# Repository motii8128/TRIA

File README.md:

# TRIA
Triple-wheel Robot for Intelligent Autonomous

# install
```
sudo apt install nlohmann-json3-dev
sudo apt install protobuf-compiler
```

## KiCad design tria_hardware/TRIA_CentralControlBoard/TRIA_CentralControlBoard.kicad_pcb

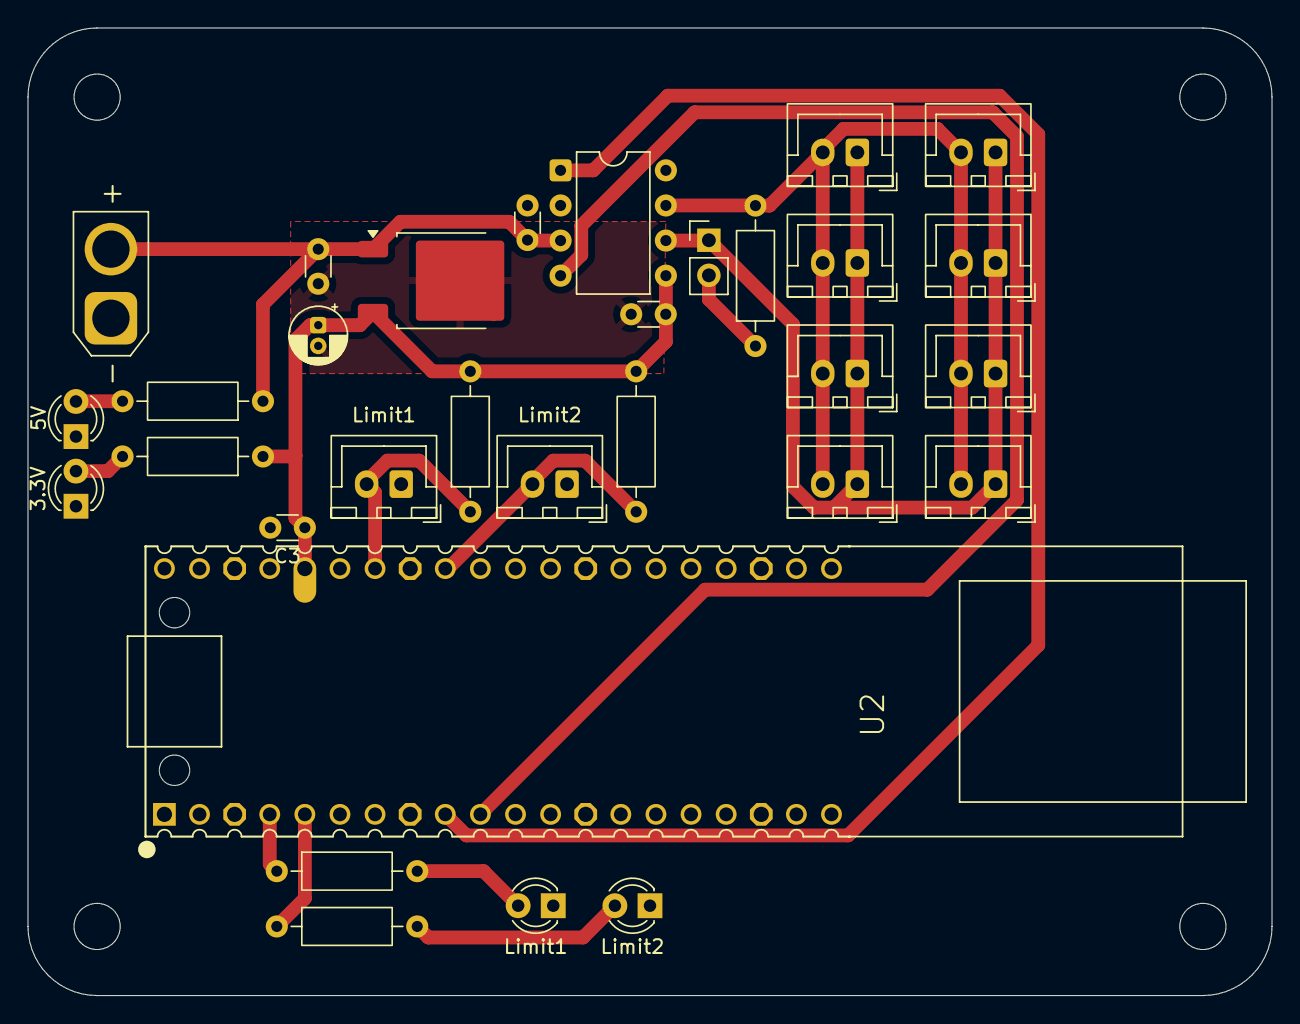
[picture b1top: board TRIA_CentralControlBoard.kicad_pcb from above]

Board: 2 copper layers, 90.0 x 70.0 mm, 31 parts (0 on the bottom side), 16 nets.

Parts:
3.3V: GREEN; LED_D3.0mm
5V: BLUE; LED_D3.0mm
C1, C3, C14, C15: 0.1u; C_Disc_D3.0mm_W1.6mm_P2.50mm
C2: 10uF16V; CP_Radial_D4.0mm_P1.50mm
J1, J3, J4, J6, J7, J8, J9, J10: CAN; JST_XH_B2B-XH-A_1x02_P2.50mm_Vertical
J2: LogicBatt; AMASS_XT30U-M_1x02_P5.0mm_Vertical
J5: resistor_enable; PinHeader_1x02_P2.54mm_Vertical
Limit1: limit_switch1; JST_XH_B2B-XH-A_1x02_P2.50mm_Vertical
Limit1#2, Limit2#2: RED; LED_D3.0mm
Limit2: limit_switch2; JST_XH_B2B-XH-A_1x02_P2.50mm_Vertical
R1, R2: 10k; R_Axial_DIN0207_L6.3mm_D2.5mm_P10.16mm_Horizontal
R3, R4, R5, R6: 1k; R_Axial_DIN0207_L6.3mm_D2.5mm_P10.16mm_Horizontal
R17: 120; R_Axial_DIN0207_L6.3mm_D2.5mm_P10.16mm_Horizontal
U1: NJM2391DL1-33; TO-252-2
U2: W6300-EVB-PICO2; W5500-EVB-PICO-TH
U9: MCP2562-E-P; DIP-8_W7.62mm

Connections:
+3.3V: C2.1, C3.1, C14.1, R1.2, R2.2, R4.1, U1.3 (VO), U2.36 (3V3(OUT)), U9.5 (Vio)
/CAN/CAN_H: J1.2, J3.2, J4.2, J6.2, J7.2, J8.2, J9.2, J10.2, R17.2, U9.7 (CANH)
/CAN/CAN_L: J1.1, J3.1, J4.1, J5.1, J6.1, J7.1, J8.1, J9.1, J10.1, U9.6 (CANL)
/CAN/CAN_RX: U2.10 (GP7), U9.4 (RXD)
/CAN/CAN_TX: U2.9 (GP6), U9.1 (TXD)
/Limit_Switch/LimitSwitch1: Limit1.2, R1.1, U2.34 (GP28)
/Limit_Switch/LimitSwitch2: Limit2.2, R2.1, U2.32 (GP27)
GNDD: 3.3V.1 (K), 5V.1 (K), C1.2, C2.2, C3.2, C14.2, C15.2, J2.1, Limit1.1, Limit1#2.1 (K), Limit2.1, Limit2#2.1 (K), U1.2 (GND), U2.3 (GND), U2.8 (GND), U2.13 (GND), U2.18 (GND), U2.23 (GND), U2.28 (GND), U2.33 (GND), U2.37 (3V3_EN), U2.38 (GND), U9.2 (VSS), U9.8 (STBY)
LED1: R5.1, U2.4 (GP2)
LED2: R6.1, U2.5 (GP3)
unnamed: 5V.2 (A), R3.2
unnamed: 3.3V.2 (A), R4.2
unnamed: Limit1#2.2 (A), R5.2
unnamed: Limit2#2.2 (A), R6.2
unnamed: J5.2, R17.1
VDD: C1.1, C15.1, J2.2, R3.1, U1.1 (VI), U9.3 (VDD)

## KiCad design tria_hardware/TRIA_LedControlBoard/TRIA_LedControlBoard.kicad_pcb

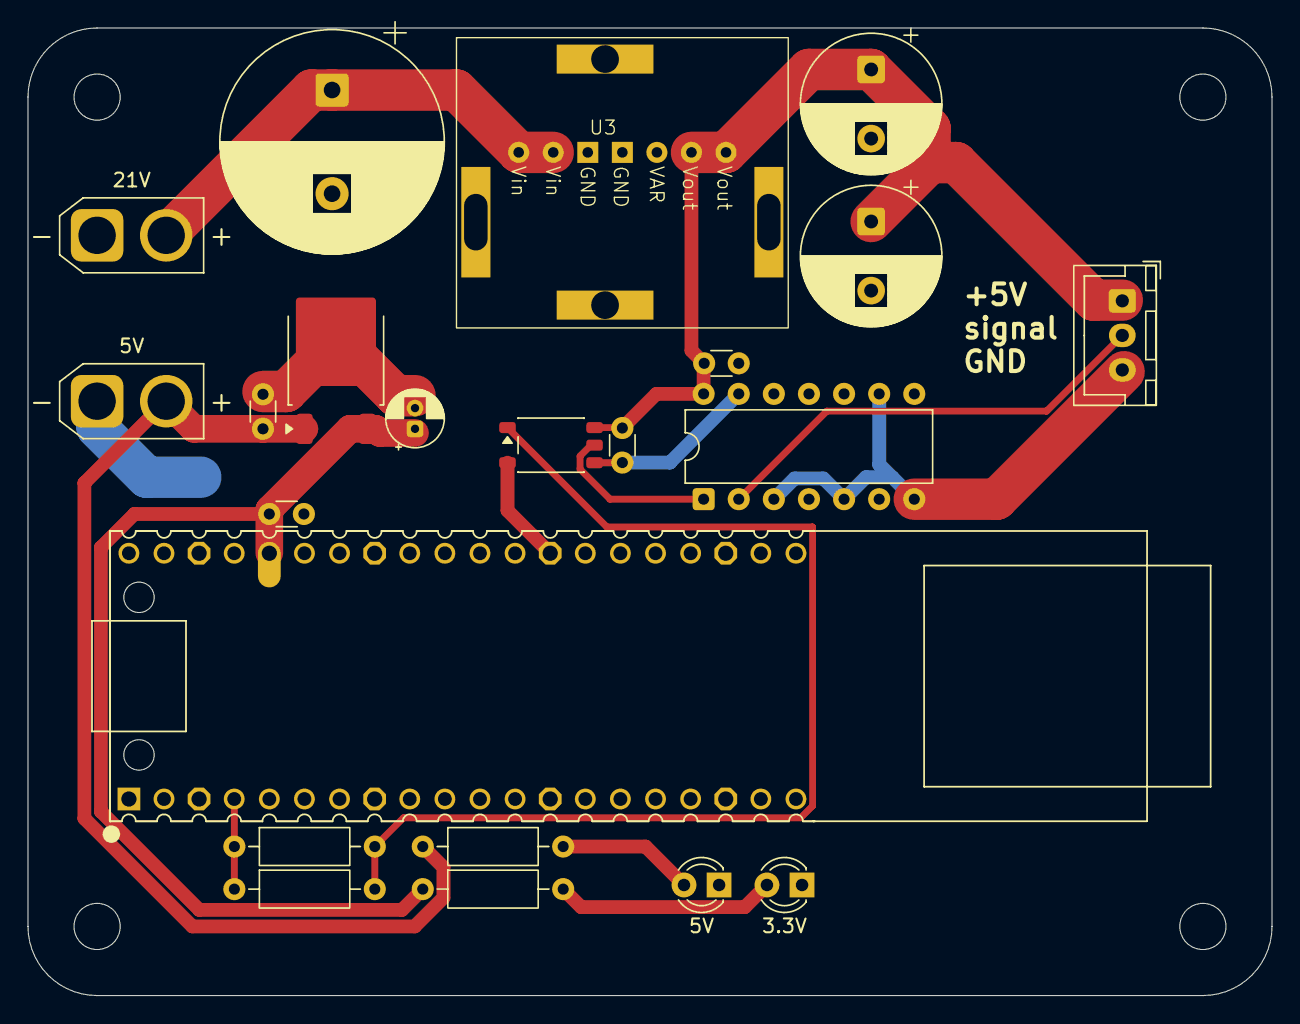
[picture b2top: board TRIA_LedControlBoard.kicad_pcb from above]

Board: 2 copper layers, 90.0 x 70.0 mm, 22 parts (0 on the bottom side), 12 nets.

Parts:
3.3V: GREEN; LED_D3.0mm
5V: LogicBatt; AMASS_XT30U-M_1x02_P5.0mm_Vertical
5V#2: BLUE; LED_D3.0mm
21V: DriveBatt; AMASS_XT30U-M_1x02_P5.0mm_Vertical
C1, C3, C7, C8: 0.1u; C_Disc_D3.0mm_W1.6mm_P2.50mm
C2: 10uF16V; CP_Radial_D4.0mm_P1.50mm
C4: 1000uF50V; CP_Radial_D16.0mm_P7.50mm
C5, C6: 1000uF25V; CP_Radial_D10.0mm_P5.00mm
R1, R2, R3, R4: 1k; R_Axial_DIN0207_L6.3mm_D2.5mm_P10.16mm_Horizontal
U1: NJM2391DL1-33; TO-252-2
U2: W6300-EVB-PICO2; W5500-EVB-PICO-TH
U3: MPD7K020S
U4: TLP2361; SO-5-6_4.55x3.7mm_P1.27mm
U5: 74HC04; DIP-14_W7.62mm
WS2812: WS2812; JST_XH_B3B-XH-A_1x03_P2.50mm_Vertical

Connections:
+3.3V: C2.1, C3.1, R4.1, U1.3 (VO), U2.36 (3V3(OUT))
+5V: C5.1, C6.1, C7.1, C8.1, U3.6 (Vout), U3.7 (Vout), U4.6 (VDD), U5.14 (VCC), WS2812.1
+BATT: 21V.2, C4.1, U3.1 (Vin), U3.2 (Vin)
/PhotoCoupler/signal_in: R1.1, R2.1, U2.4 (GP2)
/PhotoCoupler/signal_out: U5.2, WS2812.2
GND: 21V.1, C4.2, C5.2, C6.2, C7.2, C8.2, U3.3 (GND), U3.4 (GND), U4.4 (GND), U5.3, U5.5, U5.7 (GND), U5.9, U5.11, U5.13, WS2812.3
GNDD: 3.3V.1 (K), 5V.1, 5V#2.1 (K), C1.2, C2.2, C3.2, U1.2 (GND), U2.3 (GND), U2.8 (GND), U2.13 (GND), U2.18 (GND), U2.23 (GND), U2.28 (GND), U2.33 (GND), U2.37 (3V3_EN), U2.38 (GND), U4.3 (K)
unnamed: 5V#2.2 (A), R3.2
unnamed: 3.3V.2 (A), R4.2
unnamed: R1.2, R2.2, U4.1 (A)
unnamed: U4.5 (VO), U5.1
VDD: 5V.2, C1.1, R3.1, U1.1 (VI)

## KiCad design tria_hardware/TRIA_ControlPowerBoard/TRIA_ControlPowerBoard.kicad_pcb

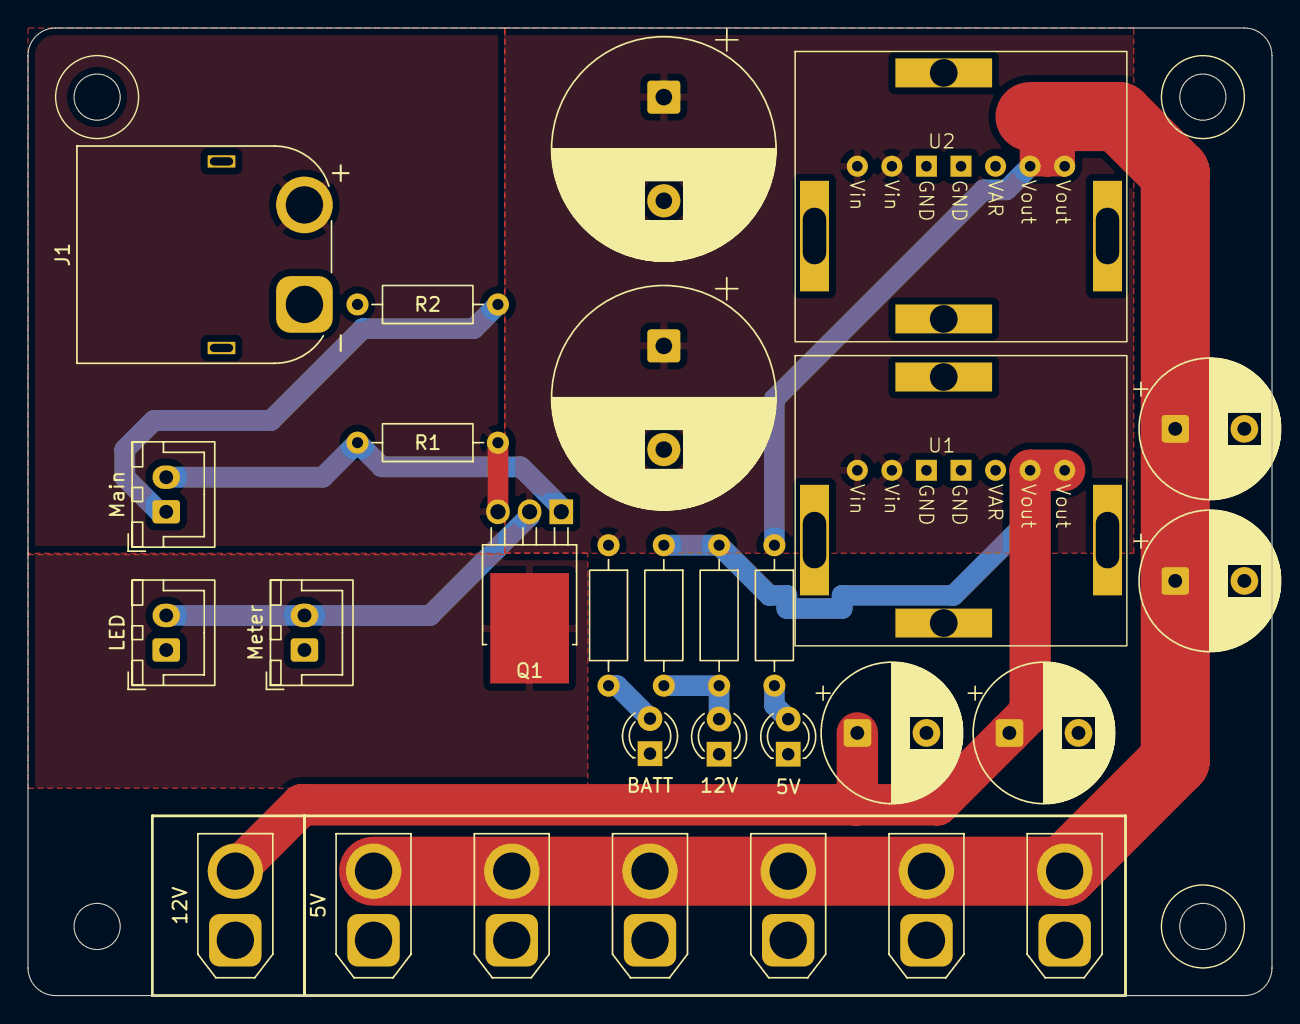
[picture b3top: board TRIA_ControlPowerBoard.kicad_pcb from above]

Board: 2 copper layers, 90.0 x 70.0 mm, 29 parts (0 on the bottom side), 10 nets.

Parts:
5V: GREEN; LED_D3.0mm
5V#2: out5V; AMASS_XT30U-F_1x02_P5.0mm_Vertical
12V: out12V; AMASS_XT30U-F_1x02_P5.0mm_Vertical
12V#2: RED; LED_D3.0mm
BATT: BLUE; LED_D3.0mm
C1, C4: 1000uF50V; CP_Radial_D16.0mm_P7.50mm
C2, C3, C5, C6: 1000uF25V; CP_Radial_D10.0mm_P5.00mm
J1: Batt; AMASS_XT60PW-M_1x02_P7.20mm_Horizontal
J2, J4, J8, J9, J10: out5V; AMASS_XT30U-F_1x02_P5.0mm_Vertical
LED: SW_LED; JST_XH_B2B-XH-A_1x02_P2.50mm_Vertical
Main: power_swtich; JST_XH_B2B-XH-A_1x02_P2.50mm_Vertical
Meter: voltage_meter; JST_XH_B2B-XH-A_1x02_P2.50mm_Vertical
Q1: MTP4835I3; TO-251-3-1EP_Horizontal_TabDown
R1, R2: 10k; R_Axial_DIN0207_L6.3mm_D2.5mm_P10.16mm_Horizontal
R3, R4, R5: 1k; R_Axial_DIN0207_L6.3mm_D2.5mm_P10.16mm_Horizontal
R6: 120; R_Axial_DIN0207_L6.3mm_D2.5mm_P10.16mm_Horizontal
U1, U2: MPD7K020S

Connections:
+5V: 5V#2.2, C5.1, C6.1, J2.2, J4.2, J8.2, J9.2, J10.2, R6.1, U2.6 (Vout), U2.7 (Vout)
+12V: 12V.2, C2.1, C3.1, R4.1, R5.1, U1.6 (Vout), U1.7 (Vout)
+BATT: C1.1, C4.1, LED.2, Meter.2, Q1.1 (D), R3.1, U1.1 (Vin), U1.2 (Vin), U2.1 (Vin), U2.2 (Vin)
GND: 5V.1 (K), 5V#2.1, 12V.1, 12V#2.1 (K), BATT.1 (K), C1.2, C2.2, C3.2, C4.2, C5.2, C6.2, J1.1, J2.1, J4.1, J8.1, J9.1, J10.1, LED.1, Meter.1, R2.2, U1.3 (GND), U1.4 (GND), U1.5 (VAR), U2.3 (GND), U2.4 (GND)
unnamed: BATT.2 (A), R3.2
unnamed: 12V#2.2 (A), R4.2, R5.2
unnamed: 5V.2 (A), R6.2
unnamed: J1.2, Q1.3 (S), R1.1
unnamed: Main.1, R2.1
unnamed: Main.2, Q1.2 (G), R1.2

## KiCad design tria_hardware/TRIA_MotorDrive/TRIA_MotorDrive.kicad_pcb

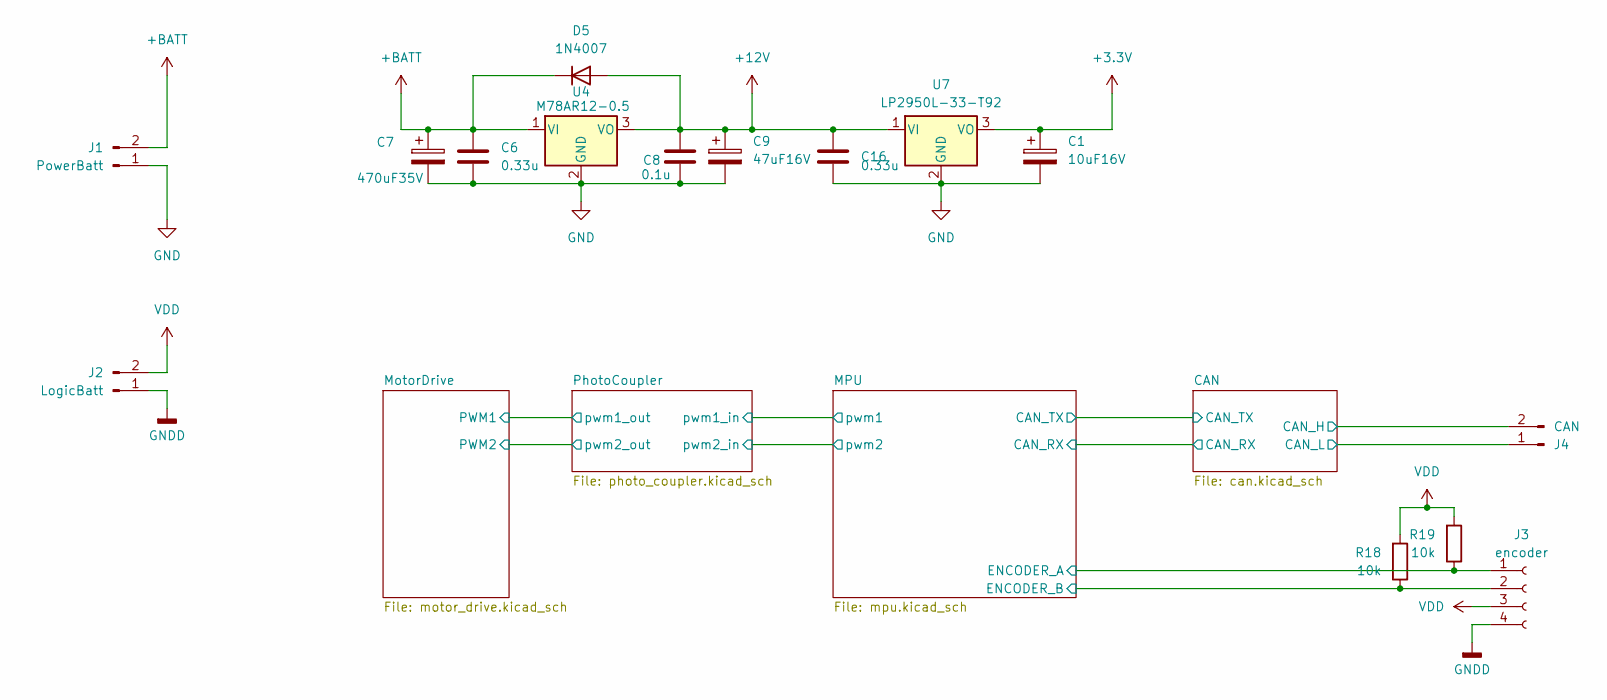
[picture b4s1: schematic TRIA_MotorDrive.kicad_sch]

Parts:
C1: 10uF16V; CP_Radial_D4.0mm_P1.50mm
C6, C16: 0.33u; C_Disc_D3.0mm_W1.6mm_P2.50mm
C7: 470uF35V; CP_Radial_D10.0mm_P5.00mm
C8: 0.1u; C_Disc_D3.0mm_W1.6mm_P2.50mm
C9: 47uF16V; CP_Radial_D5.0mm_P2.00mm
D5: 1N4007; D_DO-41_SOD81_P7.62mm_Horizontal
J1: PowerBatt; AMASS_XT60-M_1x02_P7.20mm_Vertical
J2: LogicBatt; AMASS_XT30U-M_1x02_P5.0mm_Vertical
J3: encoder; JST_XH_B4B-XH-A_1x04_P2.50mm_Vertical
J4: CAN; JST_XH_B2B-XH-A_1x02_P2.50mm_Vertical
R18, R19: 10k; R_Axial_DIN0207_L6.3mm_D2.5mm_P10.16mm_Horizontal
U4: M78AR12-0.5; m78ar033-1
U7: LP2950L-33-T92; TO-92L_Inline

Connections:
+3.3V: C1.1, U7.3 (VO); also elsewhere on the board
+12V: C8.1, C9.1, C16.1, D5.2 (A), U4.3 (VO), U7.1 (VI)
+BATT: C6.1, C7.1, D5.1 (K), J1.2, U4.1 (VI); also elsewhere on the board
/CAN/CAN_H: J4.2; also elsewhere on the board
/CAN/CAN_L: J4.1; also elsewhere on the board
/MPU/ENCODER_A: J3.1, R19.1; also elsewhere on the board
/MPU/ENCODER_B: J3.2, R18.1; also elsewhere on the board
GND: C1.2, C6.2, C7.2, C8.2, C9.2, C16.2, J1.1, U4.2 (GND), U7.2 (GND); also elsewhere on the board
GNDD: J2.1, J3.4; also elsewhere on the board
VDD: J2.2, J3.3, R18.2, R19.2; also elsewhere on the board

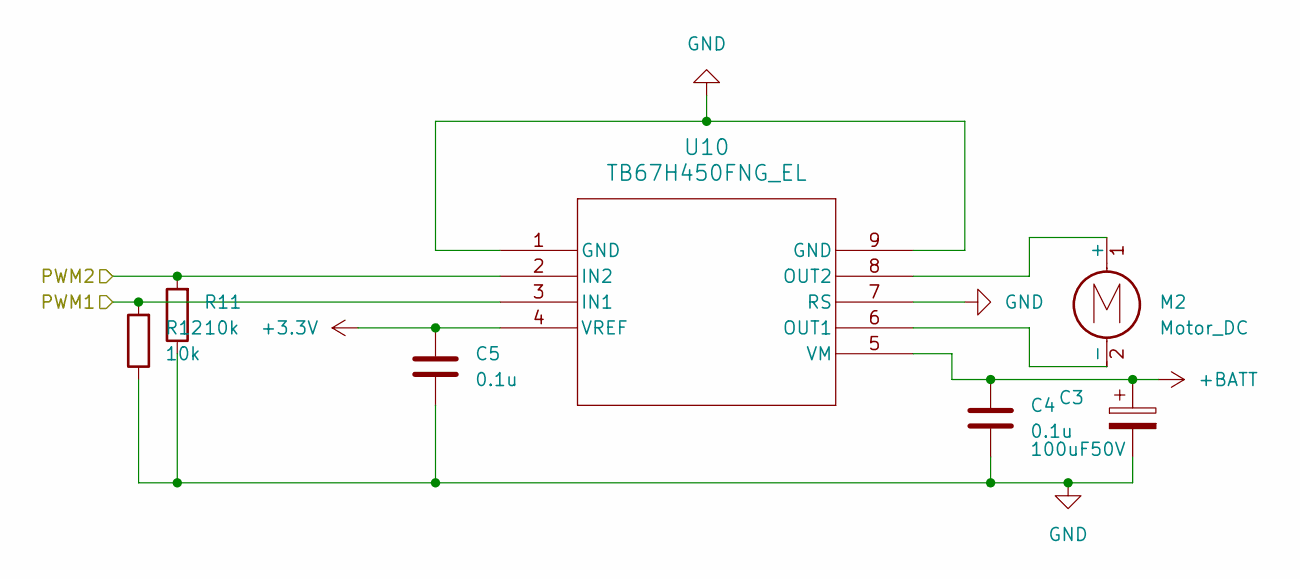
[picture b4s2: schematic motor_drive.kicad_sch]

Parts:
C3: 100uF50V; CP_Radial_D8.0mm_P3.50mm
C4, C5: 0.1u; C_Disc_D3.0mm_W1.6mm_P2.50mm
M2: Motor_DC; AMASS_XT60-F_1x02_P7.20mm_Vertical
R11, R12: 10k; R_Axial_DIN0207_L6.3mm_D2.5mm_P10.16mm_Horizontal
U10: TB67H450FNG_EL; P-HSOP8-0405-1p27-002_TOS

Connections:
+3.3V: C5.1, U10.4 (VREF); also elsewhere on the board
+BATT: C3.1, C4.1, U10.5 (VM); also elsewhere on the board
/MotorDrive/PWM1: R12.2, U10.3 (IN1); also elsewhere on the board
/MotorDrive/PWM2: R11.2, U10.2 (IN2); also elsewhere on the board
GND: C3.2, C4.2, C5.2, R11.1, R12.1, U10.1 (GND), U10.7 (RS), U10.9 (GND); also elsewhere on the board
unnamed: M2.1 (+), U10.8 (OUT2)
unnamed: M2.2 (-), U10.6 (OUT1)

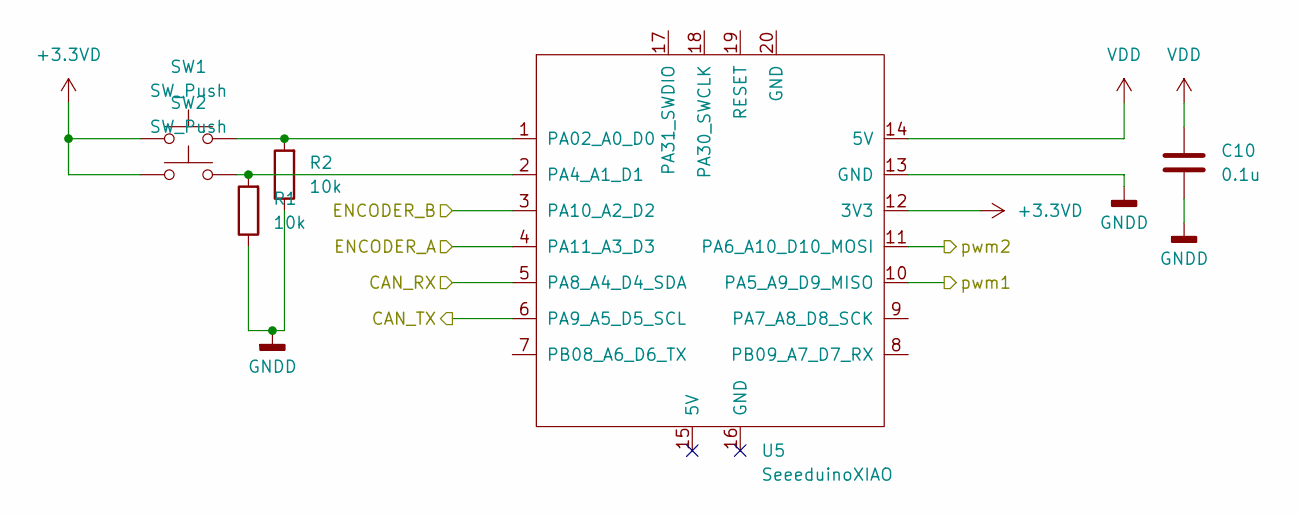
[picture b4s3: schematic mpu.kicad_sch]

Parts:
C10: 0.1u; C_Disc_D3.0mm_W1.6mm_P2.50mm
R1, R2: 10k; R_Axial_DIN0207_L6.3mm_D2.5mm_P10.16mm_Horizontal
SW1, SW2: SW_Push; SW_PUSH_6mm
U5: SeeeduinoXIAO; Seeeduino XIAO-MOUDLE14P-2.54-21X17.8MM

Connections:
+3.3VD: SW1.1, SW2.1, U5.12 (3V3); also elsewhere on the board
/CAN/CAN_RX: U5.5 (PA8_A4_D4_SDA); also elsewhere on the board
/CAN/CAN_TX: U5.6 (PA9_A5_D5_SCL); also elsewhere on the board
/MPU/ENCODER_A: U5.4 (PA11_A3_D3); also elsewhere on the board
/MPU/ENCODER_B: U5.3 (PA10_A2_D2); also elsewhere on the board
/MPU/pwm1: U5.10 (PA5_A9_D9_MISO); also elsewhere on the board
/MPU/pwm2: U5.11 (PA6_A10_D10_MOSI); also elsewhere on the board
GNDD: C10.2, R1.1, R2.1, U5.13 (GND); also elsewhere on the board
unnamed: R2.2, SW1.2, U5.1 (PA02_A0_D0)
unnamed: R1.2, SW2.2, U5.2 (PA4_A1_D1)
VDD: C10.1, U5.14 (5V); also elsewhere on the board

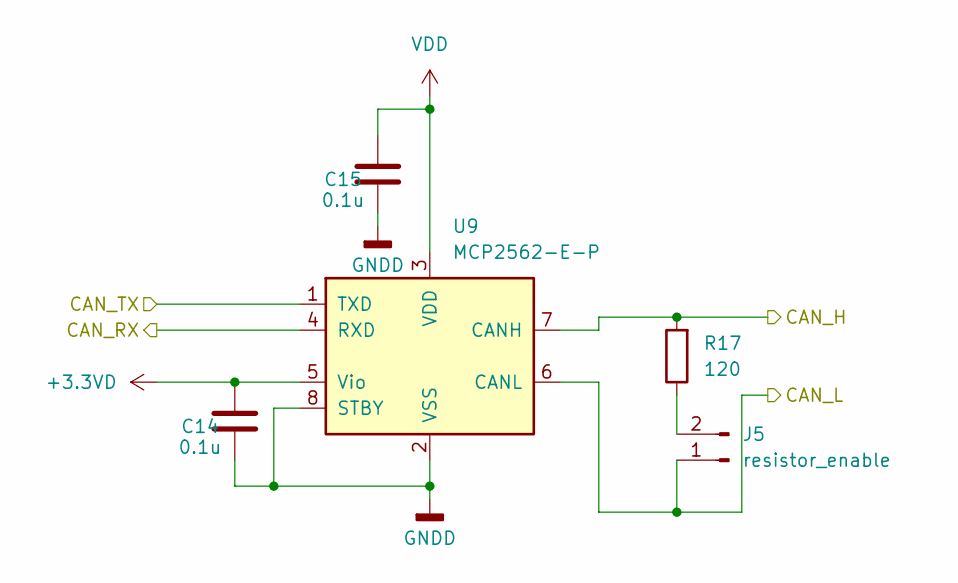
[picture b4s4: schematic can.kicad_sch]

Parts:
C14, C15: 0.1u; C_Disc_D3.0mm_W1.6mm_P2.50mm
J5: resistor_enable; PinHeader_1x02_P2.54mm_Vertical
R17: 120; R_Axial_DIN0207_L6.3mm_D2.5mm_P10.16mm_Horizontal
U9: MCP2562-E-P; DIP-8_W7.62mm

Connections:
+3.3VD: C14.1, U9.5 (Vio); also elsewhere on the board
/CAN/CAN_H: R17.2, U9.7 (CANH); also elsewhere on the board
/CAN/CAN_L: J5.1, U9.6 (CANL); also elsewhere on the board
/CAN/CAN_RX: U9.4 (RXD); also elsewhere on the board
/CAN/CAN_TX: U9.1 (TXD); also elsewhere on the board
GNDD: C14.2, C15.2, U9.2 (VSS), U9.8 (STBY); also elsewhere on the board
unnamed: J5.2, R17.1
VDD: C15.1, U9.3 (VDD); also elsewhere on the board

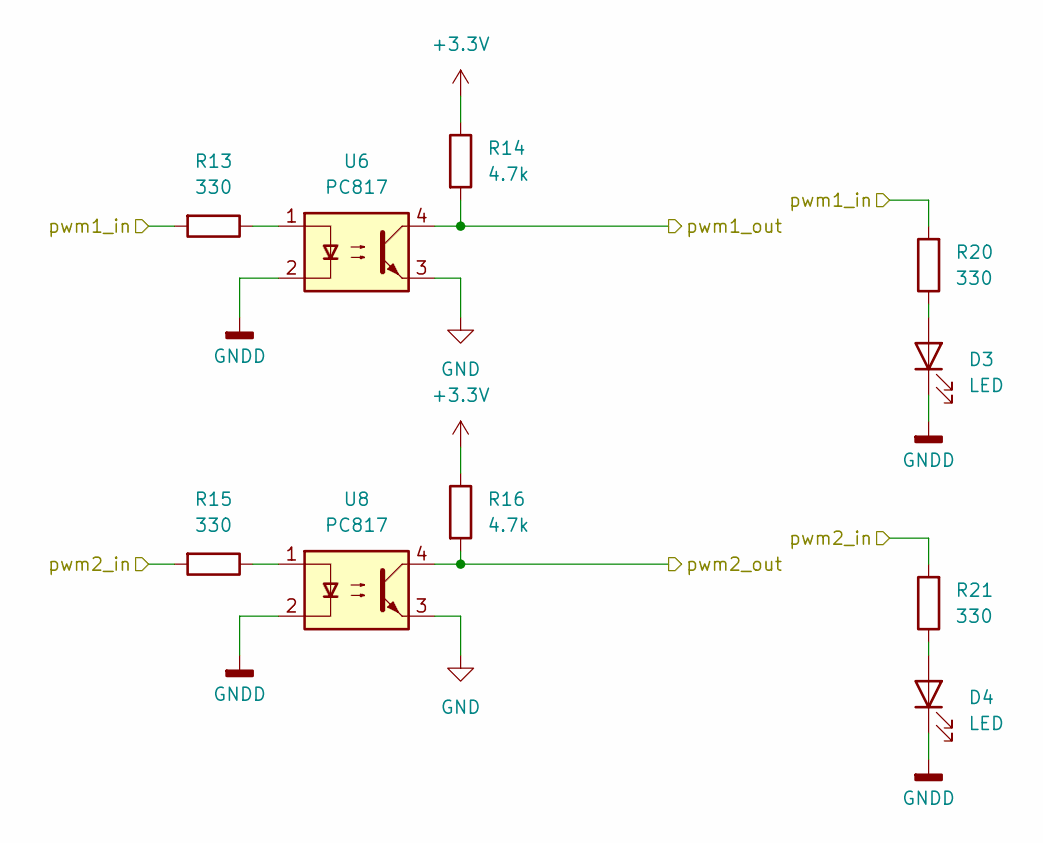
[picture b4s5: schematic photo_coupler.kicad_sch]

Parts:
D3, D4: LED; LED_D3.0mm
R13, R15, R20, R21: 330; R_1206_3216Metric_Pad1.30x1.75mm_HandSolder
R14, R16: 4.7k; R_1206_3216Metric_Pad1.30x1.75mm_HandSolder
U6, U8: PC817; DIP-4_W7.62mm

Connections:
+3.3V: R14.1, R16.1; also elsewhere on the board
/MPU/pwm1: R13.2, R20.2; also elsewhere on the board
/MPU/pwm2: R15.2, R21.2; also elsewhere on the board
/MotorDrive/PWM1: R14.2, U6.4; also elsewhere on the board
/MotorDrive/PWM2: R16.2, U8.4; also elsewhere on the board
GND: U6.3, U8.3; also elsewhere on the board
GNDD: D3.1 (K), D4.1 (K), U6.2, U8.2; also elsewhere on the board
unnamed 16: D3.2 (A), R20.1; also elsewhere on the board
unnamed 17: D4.2 (A), R21.1; also elsewhere on the board
unnamed: R13.1, U6.1
unnamed: R15.1, U8.1

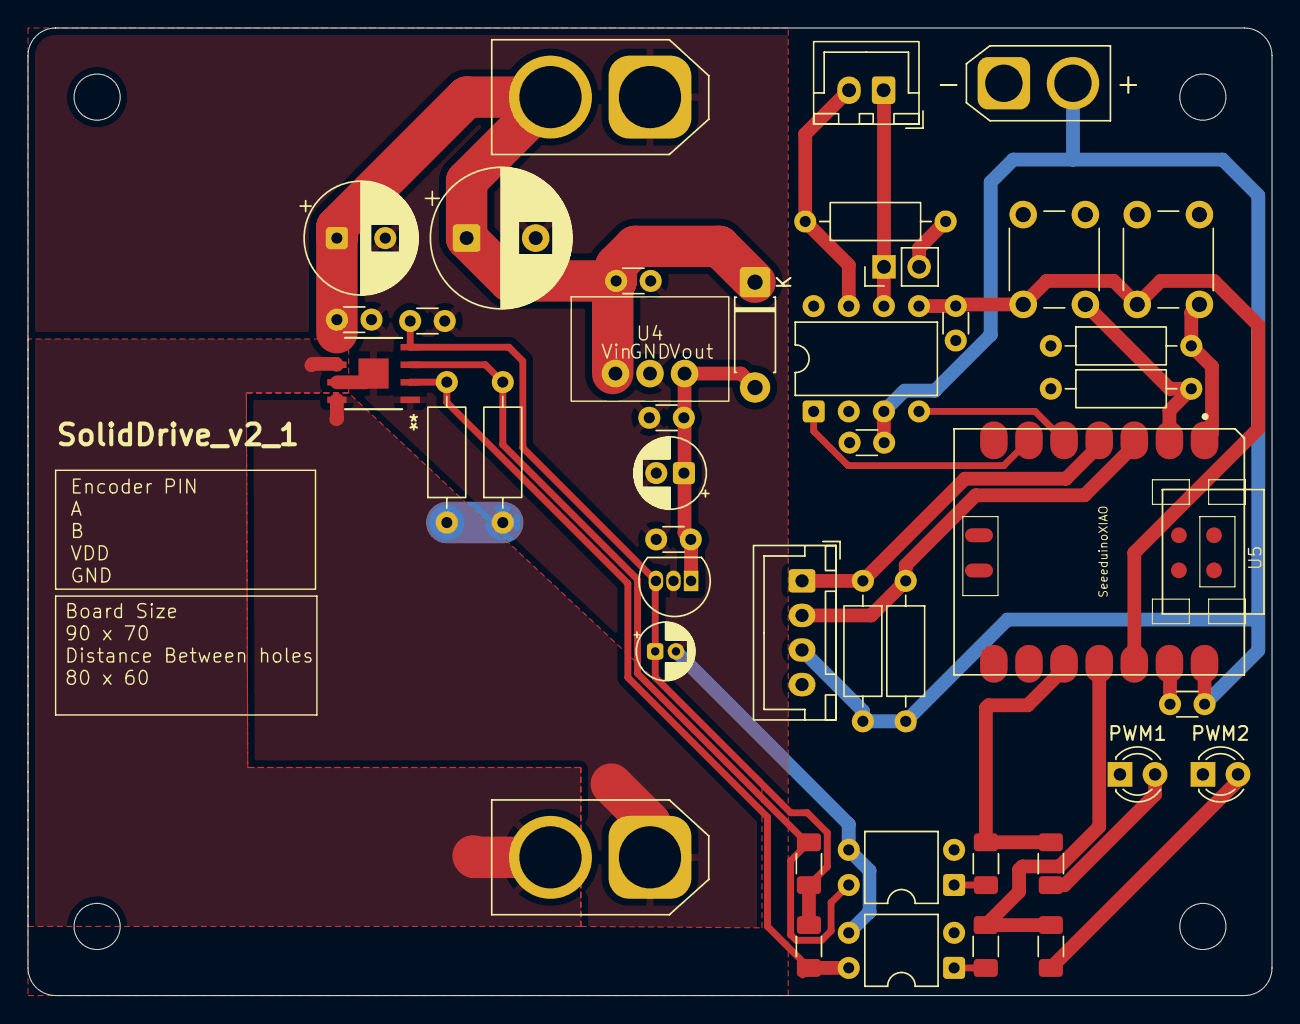
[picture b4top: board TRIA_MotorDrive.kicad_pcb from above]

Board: 2 copper layers, 90.0 x 70.0 mm, 43 parts (0 on the bottom side), 26 nets.

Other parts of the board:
PWM1, PWM2: LED; LED_D3.0mm

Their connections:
GNDD: PWM1.1 (K), PWM2.1 (K); also elsewhere on the board
unnamed 16: PWM1.2 (A); also elsewhere on the board
unnamed 17: PWM2.2 (A); also elsewhere on the board

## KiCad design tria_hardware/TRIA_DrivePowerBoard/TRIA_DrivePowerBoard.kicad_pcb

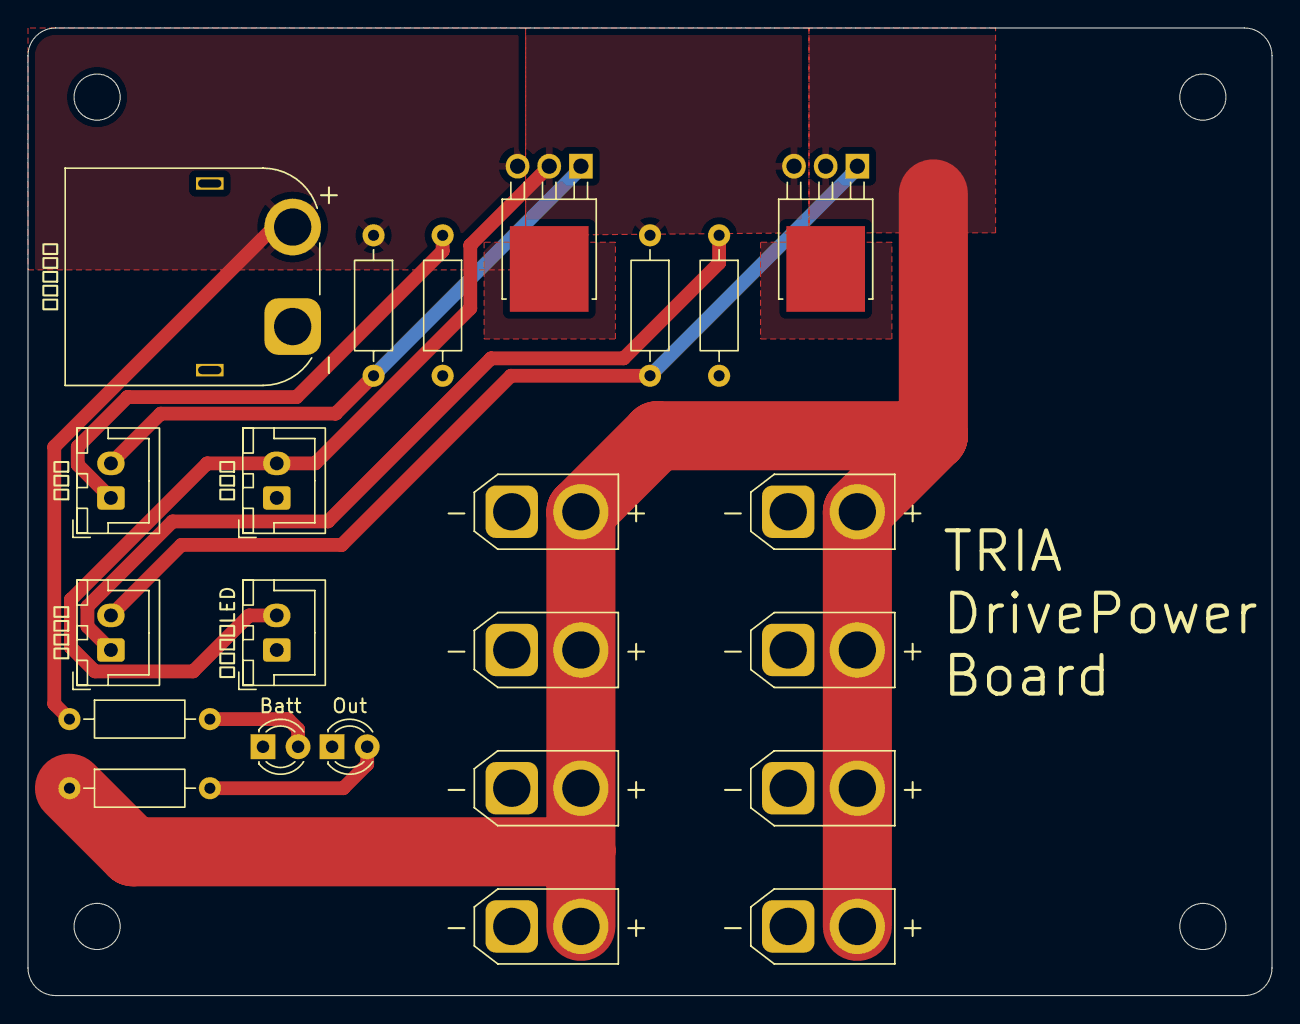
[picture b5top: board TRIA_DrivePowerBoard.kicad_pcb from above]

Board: 2 copper layers, 90.0 x 70.0 mm, 23 parts (0 on the bottom side), 10 nets.

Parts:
Batt: BLUE; LED_D3.0mm
J3, J4, J5, J8, J9, J10, J11, J12: out; AMASS_XT30U-F_1x02_P5.0mm_Vertical
Out: Green; LED_D3.0mm
Q1, Q2: MTP4835I3; TO-251-3-1EP_Horizontal_TabDown
R1, R2, R3, R4: 10k; R_Axial_DIN0207_L6.3mm_D2.5mm_P10.16mm_Horizontal
R5, R6: 1k; R_Axial_DIN0207_L6.3mm_D2.5mm_P10.16mm_Horizontal
スイッチLED: sw_led; JST_XH_B2B-XH-A_1x02_P2.50mm_Vertical
バッテリー: Batt; AMASS_XT60PW-M_1x02_P7.20mm_Horizontal
主電源: power_swtich; JST_XH_B2B-XH-A_1x02_P2.50mm_Vertical
緊急停止: emergency; JST_XH_B2B-XH-A_1x02_P2.50mm_Vertical
電圧計: voltage_meter; JST_XH_B2B-XH-A_1x02_P2.50mm_Vertical

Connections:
+BATT: Q1.3 (S), R1.1, R5.1, バッテリー.2
GND: Batt.1 (K), J3.1, J4.1, J5.1, J8.1, J9.1, J10.1, J11.1, J12.1, Out.1 (K), R2.2, R4.2, スイッチLED.1, バッテリー.1, 電圧計.1
unnamed: Batt.2 (A), R5.2
unnamed: Out.2 (A), R6.2
unnamed: R4.1, 緊急停止.1
unnamed: Q2.2 (G), R3.2, 緊急停止.2
unnamed: R2.1, 主電源.1
unnamed: Q1.2 (G), R1.2, 主電源.2
non_emergency: Q1.1 (D), Q2.3 (S), R3.1, スイッチLED.2, 電圧計.2
out: J3.2, J4.2, J5.2, J8.2, J9.2, J10.2, J11.2, J12.2, Q2.1 (D), R6.1

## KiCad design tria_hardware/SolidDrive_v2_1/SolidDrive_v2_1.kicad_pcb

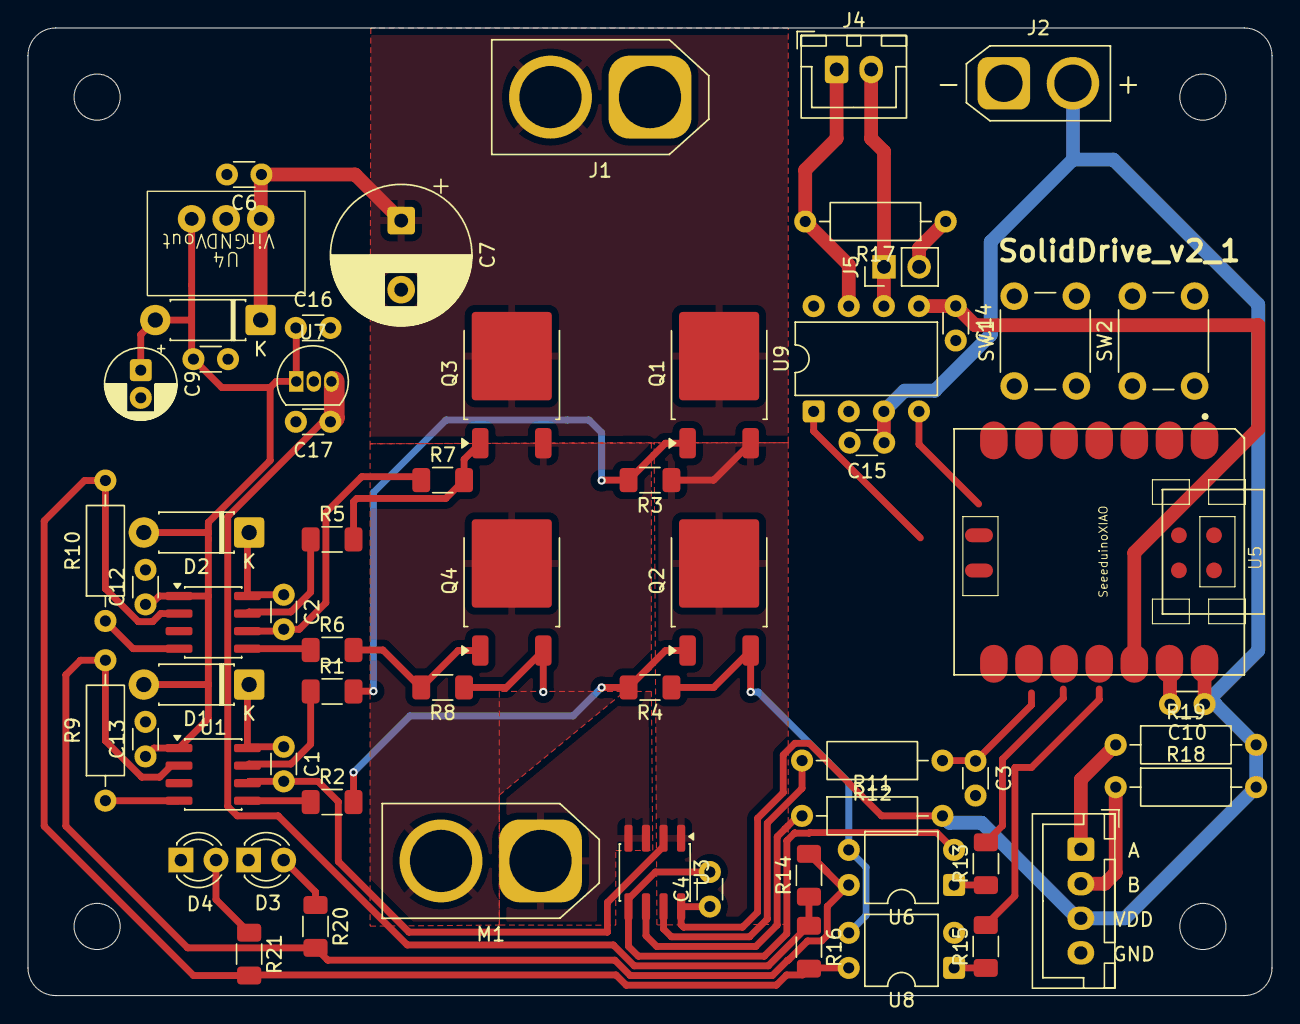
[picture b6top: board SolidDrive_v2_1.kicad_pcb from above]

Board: 2 copper layers, 90.0 x 70.0 mm, 62 parts (0 on the bottom side), 35 nets.

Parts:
C1, C2: 1u; C_Disc_D3.0mm_W1.6mm_P2.50mm
C3, C4, C8, C10, C12, C13, C14, C15, C17: 0.1u; C_Disc_D3.0mm_W1.6mm_P2.50mm
C6, C16: 0.33u; C_Disc_D3.0mm_W1.6mm_P2.50mm
C7: 470uF35V; CP_Radial_D10.0mm_P5.00mm
C9: 47uF16V; CP_Radial_D5.0mm_P2.00mm
D1, D2: 1N5819; D_DO-41_SOD81_P7.62mm_Horizontal
D3, D4: LED; LED_D3.0mm
D5: 1N4007; D_DO-41_SOD81_P7.62mm_Horizontal
J1: PowerBatt; AMASS_XT60-M_1x02_P7.20mm_Vertical
J2: LogicBatt; AMASS_XT30U-M_1x02_P5.0mm_Vertical
J3: encoder; JST_XH_B4B-XH-A_1x04_P2.50mm_Vertical
J4: CAN; JST_XH_B2B-XH-A_1x02_P2.50mm_Vertical
J5: resistor_enable; PinHeader_1x02_P2.54mm_Vertical
M1: Motor_DC; AMASS_XT60-F_1x02_P7.20mm_Vertical
Q1: MTB7D0N06RJ3; TO-252-2
Q2: LOW1; TO-252-2
Q3: HIGH2; TO-252-2
Q4: LOW2; TO-252-2
R1, R2, R5, R6: 10; R_1206_3216Metric_Pad1.30x1.75mm_HandSolder
R3, R4, R7, R8: 10k; R_1206_3216Metric_Pad1.30x1.75mm_HandSolder
R9, R10, R18, R19: 10k; R_Axial_DIN0207_L6.3mm_D2.5mm_P10.16mm_Horizontal
R11: PullUp; R_Axial_DIN0207_L6.3mm_D2.5mm_P10.16mm_Horizontal
R12: 1k; R_Axial_DIN0207_L6.3mm_D2.5mm_P10.16mm_Horizontal
R13, R15, R20, R21: 330; R_1206_3216Metric_Pad1.30x1.75mm_HandSolder
R14, R16: 4.7k; R_1206_3216Metric_Pad1.30x1.75mm_HandSolder
R17: 120; R_Axial_DIN0207_L6.3mm_D2.5mm_P10.16mm_Horizontal
SW1, SW2: SW_Push; SW_PUSH_6mm
U1, U2: IR2302; SOIC-8_3.9x4.9mm_P1.27mm
U3: ACS711xLCTR-12AB; SOIC-8_3.9x4.9mm_P1.27mm
U4: M78AR12-0.5; m78ar033-1
U5: SeeeduinoXIAO; Seeeduino XIAO-MOUDLE14P-2.54-21X17.8MM
U6, U8: PC817; DIP-4_W7.62mm
U7: TA78L05S; TO-92L_Inline
U9: MCP2562-E-P; DIP-8_W7.62mm

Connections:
+3.3V: C14.1, U5.12 (3V3), U9.5 (Vio)
+5V: C17.1, R14.1, R16.1, U7.3 (VO)
+12V: C8.1, C9.1, C12.1, C13.1, C16.1, D1.2 (A), D2.2 (A), D5.2 (A), U1.1 (VCC), U2.1 (VCC), U4.3 (VO), U7.1 (VI)
+BATT: C6.1, C7.1, D5.1 (K), J1.2, Q1.2 (D), Q3.2 (D), U4.1 (VI)
/CAN/CAN_H: J4.1, R17.2, U9.7 (CANH)
/CAN/CAN_L: J4.2, J5.1, U9.6 (CANL)
/MPU/CurrentSensor: C3.1, R12.1
/MPU/ENCODER_A: J3.1, R19.1
/MPU/ENCODER_B: J3.2, R18.1
/MotorDrive/CurrentSensor/IP+: C1.2, Q1.3 (S), Q2.2 (D), R3.1, U1.6 (VS), U3.1 (IP+), U3.2 (IP+)
/MotorDrive/CurrentSensor/IP-: M1.1 (+), U3.3 (IP-), U3.4 (IP-)
/MotorDrive/PWM1: R9.2, R14.2, R20.2, U1.2 (IN), U6.4
/MotorDrive/PWM2: R10.2, R16.2, R21.2, U2.2 (IN), U8.4
GND: C6.2, C7.2, C8.2, C9.2, C12.2, C13.2, C16.2, C17.2, D3.1 (K), D4.1 (K), J1.1, Q2.3 (S), Q4.3 (S), R4.1, R8.1, R9.1, R10.1, U1.4 (COM), U2.4 (COM), U4.2 (GND), U6.3, U7.2 (GND), U8.3
GNDD: C3.2, C4.2, C10.2, C14.2, C15.2, J2.1, J3.4, U3.5 (GND), U5.13 (GND), U6.2, U8.2, U9.2 (VSS), U9.8 (STBY)
unnamed: C1.1, D1.1 (K), U1.8 (VB)
unnamed: C2.1, D2.1 (K), U2.8 (VB)
unnamed: D3.2 (A), R20.1
unnamed: D4.2 (A), R21.1
unnamed: J5.2, R17.1
unnamed: M1.2 (-), Q3.3 (S), Q4.2 (D)
unnamed: Q1.1 (G), R1.2, R3.2
unnamed: Q2.1 (G), R2.2, R4.2
unnamed: Q3.1 (G), R5.2, R7.2
unnamed: Q4.1 (G), R6.2, R8.2
unnamed: R13.1, U6.1
unnamed: R15.1, U8.1
unnamed: R1.1, U1.7 (HO)
unnamed: R2.1, U1.5 (LO)
unnamed: R5.1, U2.7 (HO)
unnamed: R6.1, U2.5 (LO)
unnamed: C2.2, R7.1, U2.6 (VS)
unnamed: R12.2, U3.7 (VIOUT)
unnamed: R11.1, U3.6 (~FAULT)
VDD: C4.1, C10.1, C15.1, J2.2, J3.3, R11.2, R18.2, R19.2, U3.8 (VCC), U5.14 (5V), U9.3 (VDD)
